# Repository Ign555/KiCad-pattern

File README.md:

IGN555-RTC1 : FRTC8563S Module, - tested and functional

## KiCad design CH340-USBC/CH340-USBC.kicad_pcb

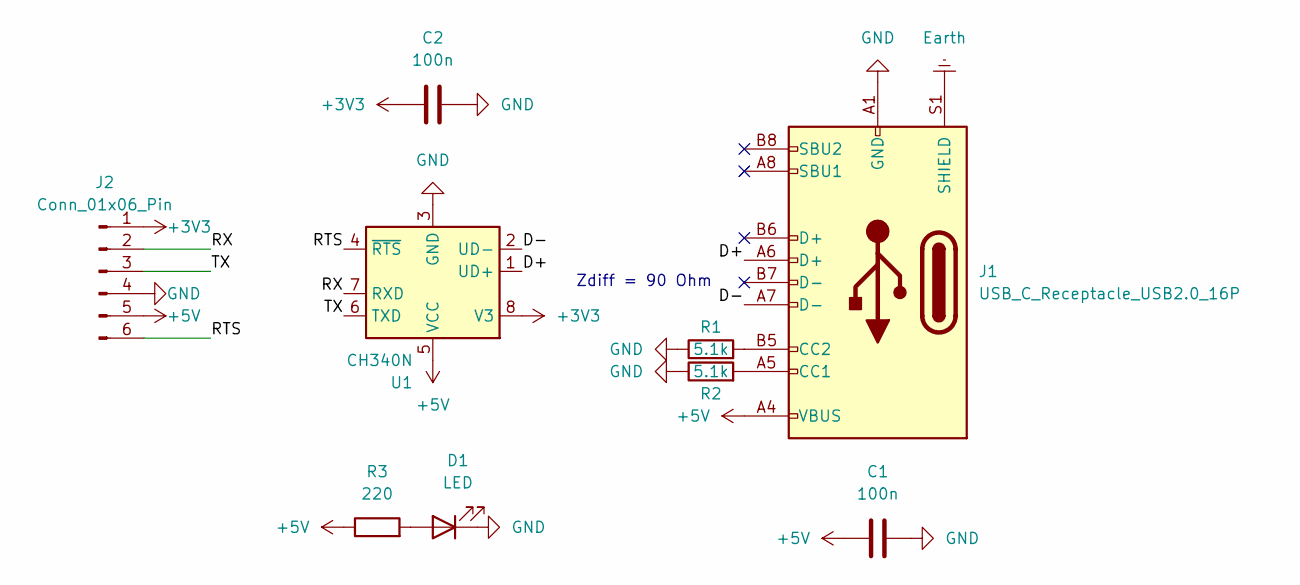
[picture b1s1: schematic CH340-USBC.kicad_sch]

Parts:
C1, C2: 100n; C_1206_3216Metric_Pad1.33x1.80mm_HandSolder
D1: LED; LED_1206_3216Metric_Pad1.42x1.75mm_HandSolder
J1: USB_C_Receptacle_USB2.0_16P; USB_C_Receptacle_G-Switch_GT-USB-7010ASV
J2: Conn_01x06_Pin; PinHeader_1x06_P2.54mm_Vertical
R1, R2: 5.1k; R_1206_3216Metric_Pad1.30x1.75mm_HandSolder
R3: 220; R_1206_3216Metric_Pad1.30x1.75mm_HandSolder
U1: CH340N; SOP-8_3.9x4.9mm_P1.27mm

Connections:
+3V3: C2.1, J2.1, U1.8 (V3)
+5V: C1.1, J1.A4 (VBUS), J1.A9 (VBUS), J1.B4 (VBUS), J1.B9 (VBUS), J2.5, R3.1, U1.5 (VCC)
/D+: J1.A6 (D+), U1.1 (UD+)
/D-: J1.A7 (D-), U1.2 (UD-)
/RTS: J2.6, U1.4 (~RTS)
/RX: J2.2, U1.7 (RXD)
/TX: J2.3, U1.6 (TXD)
Earth: J1.S1 (SHIELD)
GND: C1.2, C2.2, D1.1 (K), J1.A1 (GND), J1.A12 (GND), J1.B1 (GND), J1.B12 (GND), J2.4, R1.1, R2.1, U1.3 (GND)
unnamed: D1.2 (A), R3.2
unnamed: J1.A5 (CC1), R2.2
unnamed: J1.B5 (CC2), R1.2

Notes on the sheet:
Zdiff = 90 Ohm

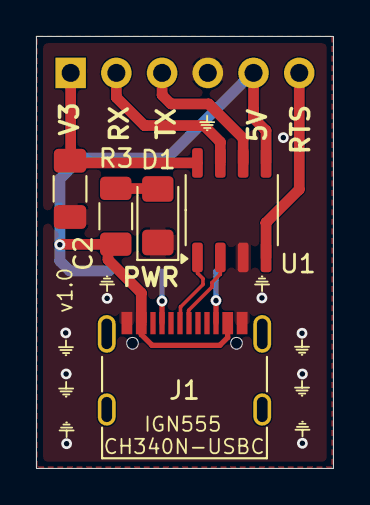
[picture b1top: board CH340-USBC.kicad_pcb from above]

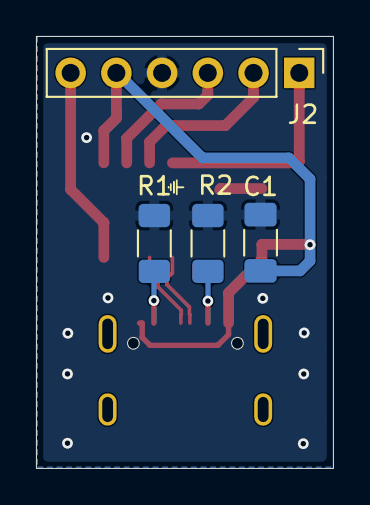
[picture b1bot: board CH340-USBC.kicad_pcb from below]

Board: 4 copper layers, 16.5 x 24.0 mm, 9 parts (4 on the bottom side), 11 nets.

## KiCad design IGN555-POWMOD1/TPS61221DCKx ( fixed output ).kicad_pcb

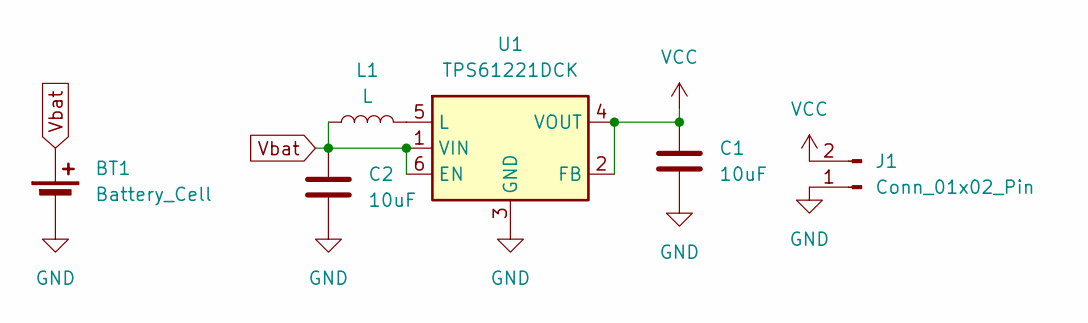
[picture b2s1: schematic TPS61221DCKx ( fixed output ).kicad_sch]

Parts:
BT1: Battery_Cell; JST_EH_B2B-EH-A_1x02_P2.50mm_Vertical
C1, C2: 10uF; C_1206_3216Metric_Pad1.33x1.80mm_HandSolder
J1: Conn_01x02_Pin; PinHeader_1x02_P2.54mm_Vertical
L1: L; L_Chilisin_BMRA00050520
U1: TPS61221DCK; Texas_R-PDSO-G6

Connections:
GND: BT1.2 (-), C1.2, C2.2, J1.1, U1.3 (GND)
unnamed: L1.2, U1.5 (L)
VCC: C1.1, J1.2, U1.2 (FB), U1.4 (VOUT)
Vbat: BT1.1 (+), C2.1, L1.1, U1.1 (VIN), U1.6 (EN)

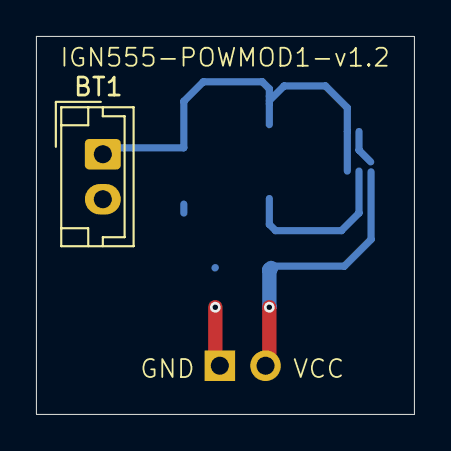
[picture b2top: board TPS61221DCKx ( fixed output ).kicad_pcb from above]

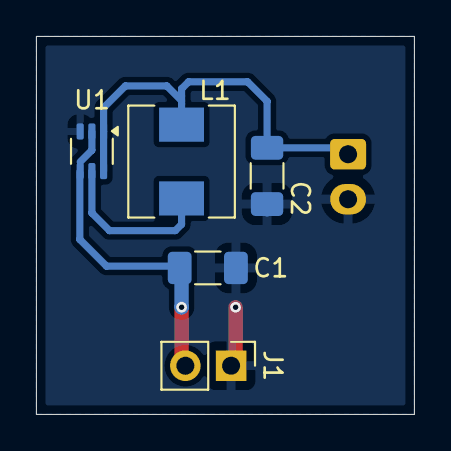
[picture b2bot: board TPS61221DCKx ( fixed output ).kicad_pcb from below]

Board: 2 copper layers, 21.0 x 21.0 mm, 6 parts (5 on the bottom side), 4 nets.

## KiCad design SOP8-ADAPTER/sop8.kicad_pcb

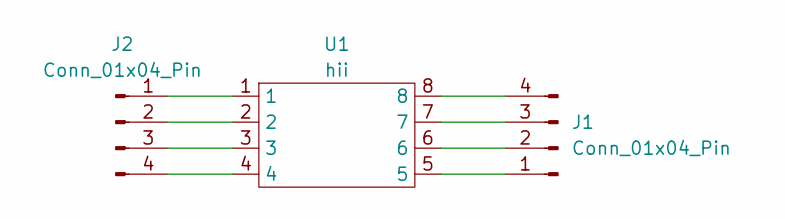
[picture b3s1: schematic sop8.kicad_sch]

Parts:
J1, J2: Conn_01x04_Pin; PinHeader_1x04_P2.54mm_Vertical
U1: hii; SOP-8_3.76x4.96mm_P1.27mm

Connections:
unnamed: J1.1, U1.5
unnamed: J1.2, U1.6
unnamed: J1.3, U1.7
unnamed: J1.4, U1.8
unnamed: J2.1, U1.1
unnamed: J2.2, U1.2
unnamed: J2.3, U1.3
unnamed: J2.4, U1.4

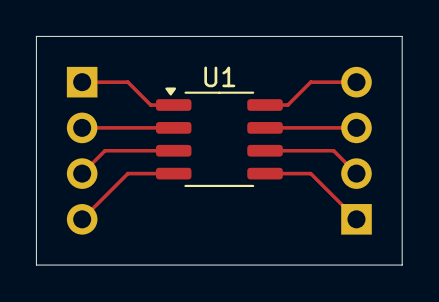
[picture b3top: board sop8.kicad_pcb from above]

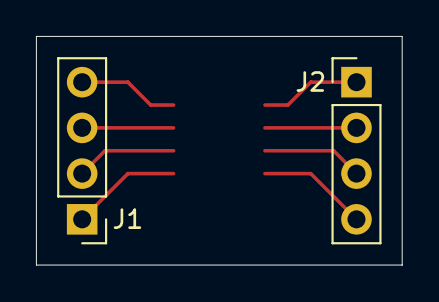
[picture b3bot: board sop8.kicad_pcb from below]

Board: 2 copper layers, 20.3 x 12.7 mm, 3 parts (2 on the bottom side), 8 nets.

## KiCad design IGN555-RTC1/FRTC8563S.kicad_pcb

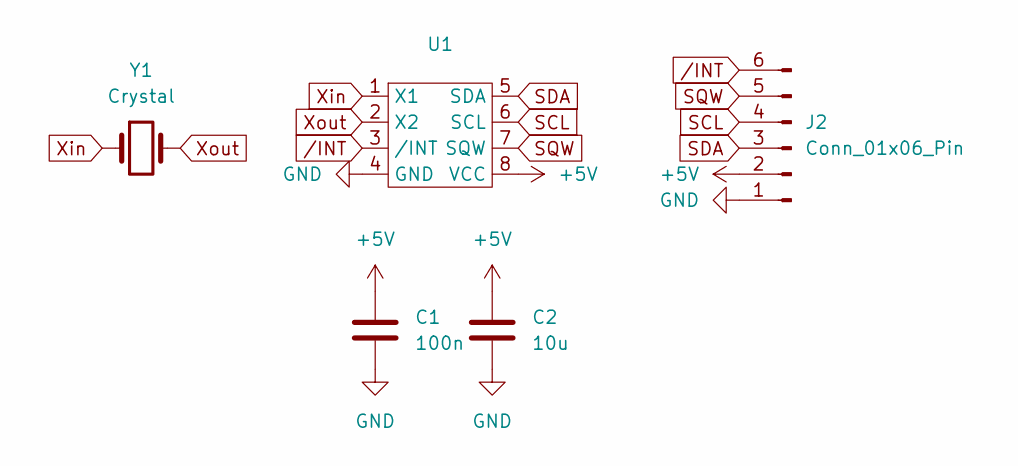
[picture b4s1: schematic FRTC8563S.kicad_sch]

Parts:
C1: 100n; C_1206_3216Metric_Pad1.33x1.80mm_HandSolder
C2: 10u; C_1206_3216Metric_Pad1.33x1.80mm_HandSolder
J2: Conn_01x06_Pin; PinHeader_1x06_P2.54mm_Vertical
U1: SOP-8_3.9x4.9mm_P1.27mm
Y1: Crystal; Crystal_C26-LF_D2.1mm_L6.5mm_Horizontal

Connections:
+5V: C1.1, C2.1, J2.2, U1.8 (VCC)
GND: C1.2, C2.2, J2.1, U1.4 (GND)
SCL: J2.4, U1.6 (SCL)
SDA: J2.3, U1.5 (SDA)
SQW: J2.5, U1.7 (SQW)
Xin: U1.1 (X1), Y1.1
Xout: U1.2 (X2), Y1.2
/INT: J2.6, U1.3 (/INT)

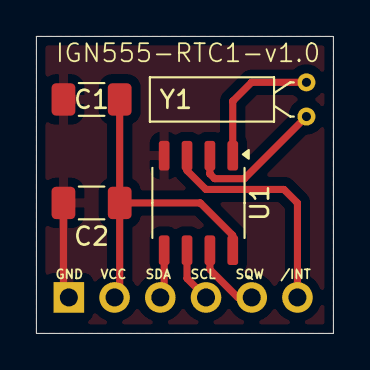
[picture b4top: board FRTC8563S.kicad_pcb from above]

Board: 2 copper layers, 16.5 x 16.5 mm, 5 parts (1 on the bottom side), 8 nets.

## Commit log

2025-11-11 Add readme
2025-12-10 Add power module based on TOS61221
2026-02-09 Move path out of the inductance zone
2026-06-29 Add USB TTL Converter
